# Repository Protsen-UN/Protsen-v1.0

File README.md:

# Protsen – Versión 2023

Este directorio contiene los avances y entregables del año **2023** del proyecto **Protsen**, desarrollado por el grupo estudiantil **Protos UN** de Bioingeniería en la Universidad Nacional de Colombia.

El enfoque de esta versión fue **construir y validar un sistema experimental con modelos anatómicos impresos en 3D y sensores FSR**, para analizar la presión ejercida por protuberancias óseas en un muñón.

---

## 📂 Estructura de carpetas

- **3D-Models/**  
  Contiene los modelos CAD y STL de la versión 2023.  
  - Variaciones de **cabeza del peroné (fibular head)**.  
  - Modelos de **tibia lateral y medial**.  
  - Variantes de la **tuberosidad tibial**.  
  - `Printing stump.stl`: muñón completo para impresión 3D.  
  - Archivos `.ipt` para edición paramétrica en Autodesk Inventor.  

- **Documentación/** *(si aplica)*  
  Reportes, protocolos de calibración y metodologías utilizadas en 2023.  

- **Electrónica/** *(si aplica)*  
  Esquemas, código o configuraciones empleadas para integrar los sensores FSR.  

---

## 🎯 Objetivos de la Versión 2023

- **Modelado CAD anatómico** de protuberancias óseas con diferentes dimensiones (flat, 5mm, 10mm, 15mm).  
- **Fabricación aditiva (impresión 3D)** del muñón y sus variaciones.  
- **Integración de sensores FSR** en zonas críticas del muñón.  
- **Calibración experimental** de los sensores para medir la presión.  
- **Documentación técnica** para futuras versiones del proyecto.  

---

## 🛠️ Requisitos técnicos

- **Software CAD**: Autodesk Inventor o Fusion 360 para editar `.ipt`.  
- **Impresora 3D** compatible con `.stl`.  
- **Material de impresión**: PLA / ABS recomendado.  
- **Sensores**: FSR calibrados para registrar presión.  

---

## 👩‍🔬 Grupo de investigación

Proyecto desarrollado por el grupo estudiantil **Protos UN – Bioingeniería**,  
Universidad Nacional de Colombia.  

---

## 📜 Licencia

Este proyecto se distribuye bajo la licencia **MIT**.  
Puedes usar, modificar y compartir libremente, dando el crédito correspondiente al grupo **Protos UN**.

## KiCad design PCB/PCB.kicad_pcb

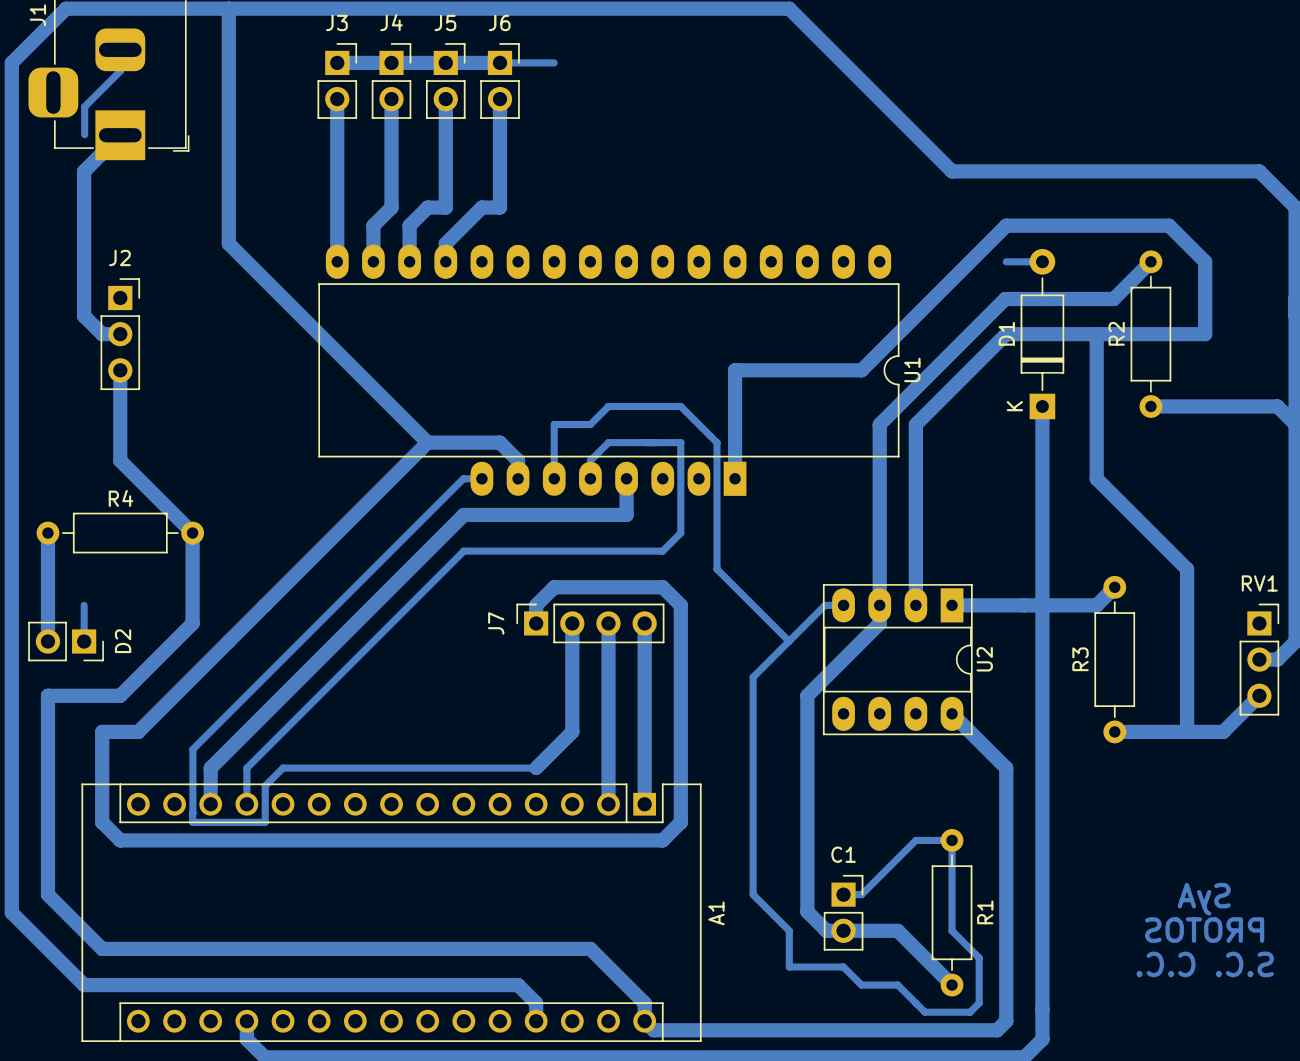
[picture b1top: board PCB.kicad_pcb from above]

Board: 2 copper layers, 18 parts (0 on the bottom side), 16 nets.

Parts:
A1: Arduino_Nano_v3.x; Arduino_Nano
C1: C_Small; PinSocket_1x02_P2.54mm_Vertical
D1: D_Zener; D_A-405_P10.16mm_Horizontal
D2: LED; PinSocket_1x02_P2.54mm_Vertical
J1: Barrel_Jack_Switch; BarrelJack_Horizontal
J2: Conn_Interruptor; PinSocket_1x03_P2.54mm_Vertical
J3: Conn_Sensor1; PinSocket_1x02_P2.54mm_Vertical
J4: Conn_Sensor2; PinSocket_1x02_P2.54mm_Vertical
J5: Conn_Sensor3; PinSocket_1x02_P2.54mm_Vertical
J6: Conn_Sensor4; PinSocket_1x02_P2.54mm_Vertical
J7: Conn_Bluetooth; PinSocket_1x04_P2.54mm_Vertical
R1, R2, R3, R4: R; R_Axial_DIN0207_L6.3mm_D2.5mm_P10.16mm_Horizontal
RV1: R_POT_TRIM; PinSocket_1x03_P2.54mm_Vertical
U1: CD74HC4067M; DIP-24_W15.24mm_LongPads
U2: LM358; DIP-8_W7.62mm_Socket_LongPads

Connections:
GND: A1.4, C1.1, D1.2, D2.1, J1.2, J3.1, J4.1, J5.1, J6.1, J7.2, R1.1, U1.12, U1.15, U2.4
unnamed: A1.1, J7.4
unnamed: A1.2, J7.3
unnamed: A1.12, U1.10
unnamed: A1.13, U1.11
unnamed: A1.19, D1.1, R3.2, U2.1
unnamed: A1.27, J7.1, R2.1, RV1.2, U1.24
unnamed: A1.30, J2.3, R4.2, U2.8
unnamed: C1.2, R1.2, R2.2, U2.3
unnamed: D2.2, R4.1
unnamed: J1.1, J2.2
unnamed: J3.2, U1.9
unnamed: J4.2, U1.8
unnamed: J5.2, U1.7
unnamed: J6.2, U1.6
unnamed: R3.1, RV1.3, U1.1, U2.2

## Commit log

2025-09-21 Primer commit limpio del proyecto Protsen - Versión 2023
2025-09-21 Adding Project Documentation
